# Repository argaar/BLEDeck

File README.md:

# BLEDeck

A custom BLE macro pad controlled by a Windows desktop application. Press a key, run a command. Switch profile, change context. Everything is driven by the app, the device is a pure peripheral.

---

## Overview

BLEDeck is a 4×4 mechanical keypad with per-key RGB lighting, a rotary encoder, and an OLED display, built around an ESP32. It communicates over BLE with a Windows app that maps each key to a shell command or executable. Profiles let you maintain separate key layouts for different workflows.

The device carries no persistent state. Every time the app connects, it pushes the current profile names and key colors to the device. This is by design, the app is the source of truth.

---

## Hardware

| Component | Part |
|-----------|------|
| MCU | ESP32 DevKitC v1 (NodeMCU-32S) |
| Keys | 16 × Gateron switches (CherryMX style) on Kailh hot-swap sockets |
| RGB | 16 × WS2812B-4020 side-emitting SMD LEDs |
| Display | SSD1306 128×64 OLED |
| Encoder | EC11 rotary encoder with push button |
| Extra buttons | CON (confirm) + BACK, mounted beside the encoder |
| Battery | Optional 1S LiPo with 15 kΩ / 4.3 kΩ voltage divider on GPIO 13 |
| PCB | Custom KiCad design, v1.1 (files under `pcb/`) |

---

## Repository Layout

```
BLEDeck/
├── firmware/          PlatformIO project (ESP32 Arduino)
│   └── src/
│       ├── main.cpp            Main loop, BLE callbacks, all handlers
│       ├── configuration.h     Pin map, BLE limits, battery constants
│       ├── protocolparser.h    Binary protocol definition + packet parser
│       ├── ota_manager.h/.cpp  WiFi OTA update manager (ElegantOTA)
│       ├── menu.h              Simple OLED settings menu
│       ├── images.h            XBM splash/lock screen bitmaps
│       └── credentials.h       WiFi + OTA password (gitignored, see below)
├── windows_app/       PyQt5 desktop application
│   ├── main.py                 BLEDeck GUI, BLE lifecycle, notification dispatch
│   ├── key_button.py           KeyButton widget
│   ├── ble_protocol.py         Packet builders, parsers, opcode constants
│   ├── ble_client.py           BleakClient re-export, BLE UUIDs, simulator factory
│   ├── profile_manager.py      Load/save profiles.json
│   ├── app_settings.py         Persistent app-level settings (preferred device MAC, …)
│   ├── action_runner.py        Command/macro dispatch with re-entrancy guard
│   ├── macro_models.py         Immutable step types + JSON serialization
│   ├── macro_recorder.py       pynput-based recorder with window anchor detection
│   ├── macro_player.py         Synchronous macro playback
│   ├── macro_dialog.py         MacroDialog QDialog (record, edit, reorder, test)
│   ├── win32_utils.py          Windows API helpers (window/monitor detection)
│   └── tests/                  Pytest suite
│       ├── test_ble_protocol.py
│       ├── test_profile_manager.py
│       ├── test_action_runner.py
│       └── test_macro_models.py
├── simulator/         BLE device simulator (no hardware needed)
│   ├── __main__.py             Entry point: python -m simulator [--ble]
│   ├── _context.py             Module-level singletons (DeviceState, active client)
│   ├── device_state.py         Simulated device state
│   ├── command_handler.py      PC→Device command handler
│   ├── event_emitter.py        Device→PC event builders
│   ├── ble_server.py           Real BLE via WinRT GattServiceProvider (Mode B)
│   ├── fake_bleak_client.py    In-process loopback (Mode A)
│   ├── cli.py                  Interactive REPL
│   └── tests/                  Pytest suite
├── pcb/               KiCad schematic + layout + Gerbers
├── docs/              Protocol reference and debugging guides
│   ├── ble_protocol_reference.md
│   ├── protocol_debugging.md
│   └── hex_quick_reference.md
└── debug/
    └── protocol_decoder.py     CLI tool to decode raw BLE packets
```

---

## Firmware

Full setup and configuration details: [`firmware/README.md`](firmware/README.md)

### Features

- **BLE GATT server** - custom service with a TX (notify) and RX (write) characteristic
- **Binary protocol** - compact framed packets: `0xAA | OPCODE | LENGTH(2B) | PAYLOAD`; max payload 256 bytes
- **Profile management** - up to 10 profiles; names and current index are pushed by the app on connect
- **Rotary encoder** - cycles through profiles when the app is connected; plays an idle RGB animation when disconnected
- **Per-key RGB** - 16 WS2812B LEDs, colors set individually or all at once by the app
- **OLED display** - shows current profile name, BLE connection status, and battery percentage
- **Battery monitoring** - ADC reading every 30 s, 5-sample rolling average, reported to the app via opcode `0x85`
- **Workstation lock** - when locked by the app, the OLED dims and shows a lock icon; all key events are suppressed
- **OTA updates** - long-press the encoder push button to open the settings menu, select *OTA Update*; the device connects to WiFi (or falls back to an AP) and serves the ElegantOTA web UI
- **`OP_HELLO` / `OP_DEVICE_TELEMETRY` handshake** - on connect the app sends `OP_HELLO` with its protocol/app version, the device replies with telemetry (firmware version, uptime, free heap, BLE error count)
- **OTA HTTP auth rate-limit infrastructure** - 5 failed logins within 60 s trigger a 5-minute lockout (trigger awaits an ElegantOTA upstream hook)

### Firmware Setup

1. Install [PlatformIO](https://platformio.org/).
2. Copy `firmware/src/credentials.h.example` → `firmware/src/credentials.h` and fill in:
   ```cpp
   #define OTA_WIFI_SSID     "your_ssid"
   #define OTA_WIFI_PASSWORD "your_wifi_password"
   #define OTA_HTTP_PASSWORD "your_ota_http_password"
   ```
3. Build and flash:
   ```bash
   cd firmware
   pio run --target upload
   ```

### Build a personalized firmware via GitHub Actions (no toolchain)

Don't want to install PlatformIO? You can have GitHub build a firmware binary
with **your own** WiFi + OTA credentials baked in and email it to you. The
`Build Personalized Firmware` workflow handles it.

1. **Fork** this repository to your own GitHub account (Actions and secrets run
   under your fork, not the upstream repo).
2. In your fork, add two repository secrets under
   **Settings → Secrets and variables → Actions → New repository secret**:
   - `MAIL_USERNAME` — the Gmail address that sends the build
   - `MAIL_PASSWORD` — a Gmail [App Password](https://support.google.com/accounts/answer/185833)
     for that account (requires 2-Step Verification; your normal password will
     not work)
3. Open the **Actions** tab → **Build Personalized Firmware** →
   **Run workflow**, and fill in:
   - `wifi_ssid`, `wifi_password` — the network the device joins for OTA
   - `ota_http_password` — the password for the OTA upload page
   - `recipient_email` — where to send the finished `firmware.bin`
4. Wait for the run to finish (a few minutes). The compiled `firmware.bin`
   arrives by email; flash it to the ESP32 with ElegantOTA or `esptool`.

> **Spam note:** the email is sent from a personal Gmail account with an
> attachment, so it can land in **Spam/Junk**. If it doesn't show up in your
> inbox within a few minutes, check there and mark it *Not spam*.

> **Privacy note:** the credentials you enter are masked in the build logs and
> the generated `credentials.h` is deleted at the end of the run, but the
> finished binary still contains them and travels through Gmail. Use this for
> personal networks, not shared/sensitive ones.

---

## Windows App

Full setup and usage details: [`windows_app/README.md`](windows_app/README.md)

### Features

- Scan and connect to BLEDeck over BLE (auto-reconnect optional)
- **Per-key configuration** - label, RGBW color (with color picker + brightness slider), action
- **Two action types per key** - shell command (via `subprocess`) or recorded macro
- **Macro recorder** - capture mouse clicks and keystrokes; replay them on key press
  - Per-click window/monitor-relative coordinates: clicks are anchored to the window or monitor they were recorded on, so playback works even if windows have moved
  - Multi-monitor support: monitors indexed by left edge (0 = leftmost)
  - Edit individual steps, drag-to-reorder, delete steps, test-run from the dialog
- **Profile management** - create, rename, save, and delete profiles; stored in `profiles.json`
- **Live RGB sync** - changing a key color sends the update to the device immediately
- **Battery indicator** - displays the battery percentage reported by the device
- **System tray** - minimises to tray, double-click or single-click to restore
- On connect: pushes all profile names, then the current profile index + RGB colors
- **Rotating debug log** at `%APPDATA%\BLEDeck\logs\bledeck.log` (5 × 20 MB rotation, 100 MB cap; KEEP_ALIVE traffic filtered out)
- **Preferred device MAC pinning** + **exponential reconnect backoff** (10 s → doubles per failed attempt → 5 min cap; resets on success)
- **High-risk command-token warning** on profile load — flags commands containing tokens such as `powershell`, `cmd /c`, `iex`, `curl … | iex`, `bitsadmin`, `mshta` before they can run
- **Macro recorder auto-stop** after 60 s of idle keyboard / mouse activity

### App Setup

```bash
cd windows_app
pip install -r requirements.txt
python main.py
```

> Python 3.12 or later required. Tested on Windows 11.

### Development Without Hardware

A device simulator is included — no physical BLEDeck required.

Loopback mode (default): no Bluetooth, instant connect. Pick the row for your shell:

| Shell       | Command |
|-------------|---------|
| cmd.exe     | `set BLEDECK_SIM=1 && python windows_app\main.py` |
| PowerShell  | `$env:BLEDECK_SIM=1; python windows_app\main.py` |
| Git Bash    | `BLEDECK_SIM=1 python windows_app/main.py` |

Real BLE mode (two machines): simulator on Machine A, app on Machine B:

```bash
python -m simulator --ble
```

Full details: [`simulator/README.md`](simulator/README.md)

---

## BLE Protocol

Full reference: [`docs/ble_protocol_reference.md`](docs/ble_protocol_reference.md)

| Direction | Opcodes |
|-----------|---------|
| PC → Device | `0x01` KEEP_ALIVE, `0x02` CHANGE_PROFILE, `0x03` SYNC_PROFILES, `0x04` SET_RGB_KEY, `0x05` SET_ALL_RGB_KEYS, `0x06` LOCK_DEVICE, `0x07` HELLO |
| Device → PC | `0x81` KEEP_ALIVE_REPLY, `0x82` PROFILE_CHANGED, `0x83` BUTTON_PRESSED, `0x84` KEY_PRESSED, `0x85` BATTERY_STATUS, `0x86` DEVICE_TELEMETRY |

To decode a raw packet from the log:
```bash
cd debug
python protocol_decoder.py "aa 85 00 01 48"
# or interactive:
python protocol_decoder.py
```

For advanced debugging see [`docs/protocol_debugging.md`](docs/protocol_debugging.md)
If you're interested in understanding the protocol, take a look at [`docs/hex_quick_reference.md`](docs/hex_quick_reference.md)

---

## Intended Use

BLEDeck is designed for Windows power users who want a physical shortcut pad without writing firmware macros. Key assignments live entirely in the app, change them without reflashing.

Typical profiles:
- **Dev** - open IDE, terminal, browser, run build script
- **Media** - control Spotify, OBS, volume
- **Gaming** - push-to-talk, clips, Discord mute
- **Comms** - join meeting, mute mic, share screen

The rotary encoder switches between profiles. The three encoder-side buttons (CON, BACK, PUSH) send named button events to the app, which can be mapped to any action.

---

## Limitations

- **Windows only** - the desktop app uses PyQt5, bleak, and ctypes Win32 APIs; no macOS or Linux app exists yet
- **App required** - the device does not persist colors or profile names; it resets to defaults when the app disconnects. This is intentional
- **10 profiles max, 16 keys per profile**
- **BLE range** - approximately 10 m in open space; walls reduce this
- **Battery gauge accuracy** - ±5%, based on a two-resistor voltage divider and a 5-sample average; calibrated for 1S LiPo (3.2 V – 4.2 V)
- **Macro recorder captures press events only** - release timing and mouse movement paths are not recorded

---

## PCB

Custom two-layer board designed in KiCad. Gerbers for JLCPCB are included under `pcb/`. Parts list and supplier links are in [`pcb/README.md`](pcb/README.md).

Current version: **v1.1**

---

## STLs

3D Models ready to be printed in PLA are available under `enclosure/stls` folder.

Ideally you need to assemble parts in the order:

- [PushButton.stl](enclosure/stls/PushButton.stl) (x2)
- [KeyboardLayer.stl](enclosure/stls/KeyboardLayer.stl)
- [BatteryTop.stl](enclosure/stls/BatteryTop.stl)
- [BatteryLayer.stl](enclosure/stls/BatteryLayer.stl)
- [Bottom.stl](enclosure/stls/Bottom.stl)

---

## License

Firmware and application source code are licensed under the [MIT License](LICENSE).

Hardware design files (PCB, schematics) and third-party component symbols/footprints retain their original licenses as listed in [`pcb/README.md`](pcb/README.md). The custom `oledknob.step` footprint is non-commercial use only.

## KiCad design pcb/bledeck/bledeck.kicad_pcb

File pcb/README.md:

# Parts list

### LED RGB WS2812b SMD 4020
https://jlcpcb.com/partdetail/Worldsemi-WS2812B4020/C965557

### Through Hole Resistor 2.2*6.5 250mW (15k + 4.3k)
Battery voltage divider on GPIO 13 (R1=15k top to BAT+, R2=4.3k bottom to GND).
https://jlcpcb.com/partdetail/59662-MFR0W4F1502A50/C58617
https://jlcpcb.com/partdetail/NTEElectronics-QW243/C6262373

### ESP32 DevKitC v1
https://lastminuteengineers.com/esp32-pinout-reference/
https://www.adrirobot.it/modulo-esp32-devkit-v1-con-wifi-e-bluetooth-ble/

### OLED (SSD1306) + Knob (EC11 rotary encoder)
https://it.aliexpress.com/item/1005009186762942.html

### Gateron Switches (CherryMX Style)
https://keychron.it/products/gateron-g-pro-3-0-switch?variant=51681846395247
https://it.aliexpress.com/item/1005006376024657.html

### Switch Transparent Cover
https://it.aliexpress.com/item/1005006821410180.html

### Kahil Hot swappable sockets
https://splitkb.com/products/kailh-hotswap-sockets
https://www.amazon.it/dp/B0DJKTNDHF
https://it.aliexpress.com/item/1005004654079817.html

### Adesive TPU Pads
https://it.aliexpress.com/item/1005006390636772.html

# Resources licenses

### Symbols

- ESP32-DEVKIT-V1.kicad_sym - https://www.snapeda.com/parts/ESP32-DEVKIT-V1/Do+it/view-part/ - CC-BY-SA
- PG151101S11.kicad_sym - https://www.snapeda.com/parts/PG151101S11/Kailh/view-part/ - CC-BY-SA
- WS2812B-4020.kicad_sym - https://www.snapeda.com/parts/WS2812B-4020/Worldsemi/view-part/ - CC-BY-SA

### Footprints

- MODULE_ESP32_DEVKIT_V1.kicad_mod - https://www.snapeda.com/parts/ESP32-DEVKIT-V1/Do+it/view-part/ - CC-BY-SA
- Kailh_socket_MX.kicad_mod - https://github.com/daprice/keyswitches.pretty - CC-BY-SA 4
- oled_rotary.kicad_mod - Custom Made under MIT License
- PinHeader_1x02_P2.54mm_Vertical.kicad_mod - https://gitlab.com/kicad/libraries/kicad-footprints/ - CC-BY-SA 4
- WS2812B-4020.kicad_mod - https://www.snapeda.com/parts/WS2812B-4020/Worldsemi/view-part/ - CC-BY-SA

### 3D Models

- CherryMX Switch.step - https://github.com/foostan/kbd - MIT
- ESP32-DEVKIT-V1.step - https://www.snapeda.com/parts/ESP32-DEVKIT-V1/Do+it/view-part/ - CC-BY-SA
- kailh_hotswap_socket.step - https://www.snapeda.com/parts/PG151101S11/Kailh/view-part/ - CC-BY-SA
- oledknob.step - https://grabcad.com/library/1-3-oled-ec11-1 - No commercial use
- WS2812B-4020--3DModel-STEP-269445.STEP - https://www.snapeda.com/parts/WS2812B-4020/Worldsemi/view-part/ - CC-BY-SA

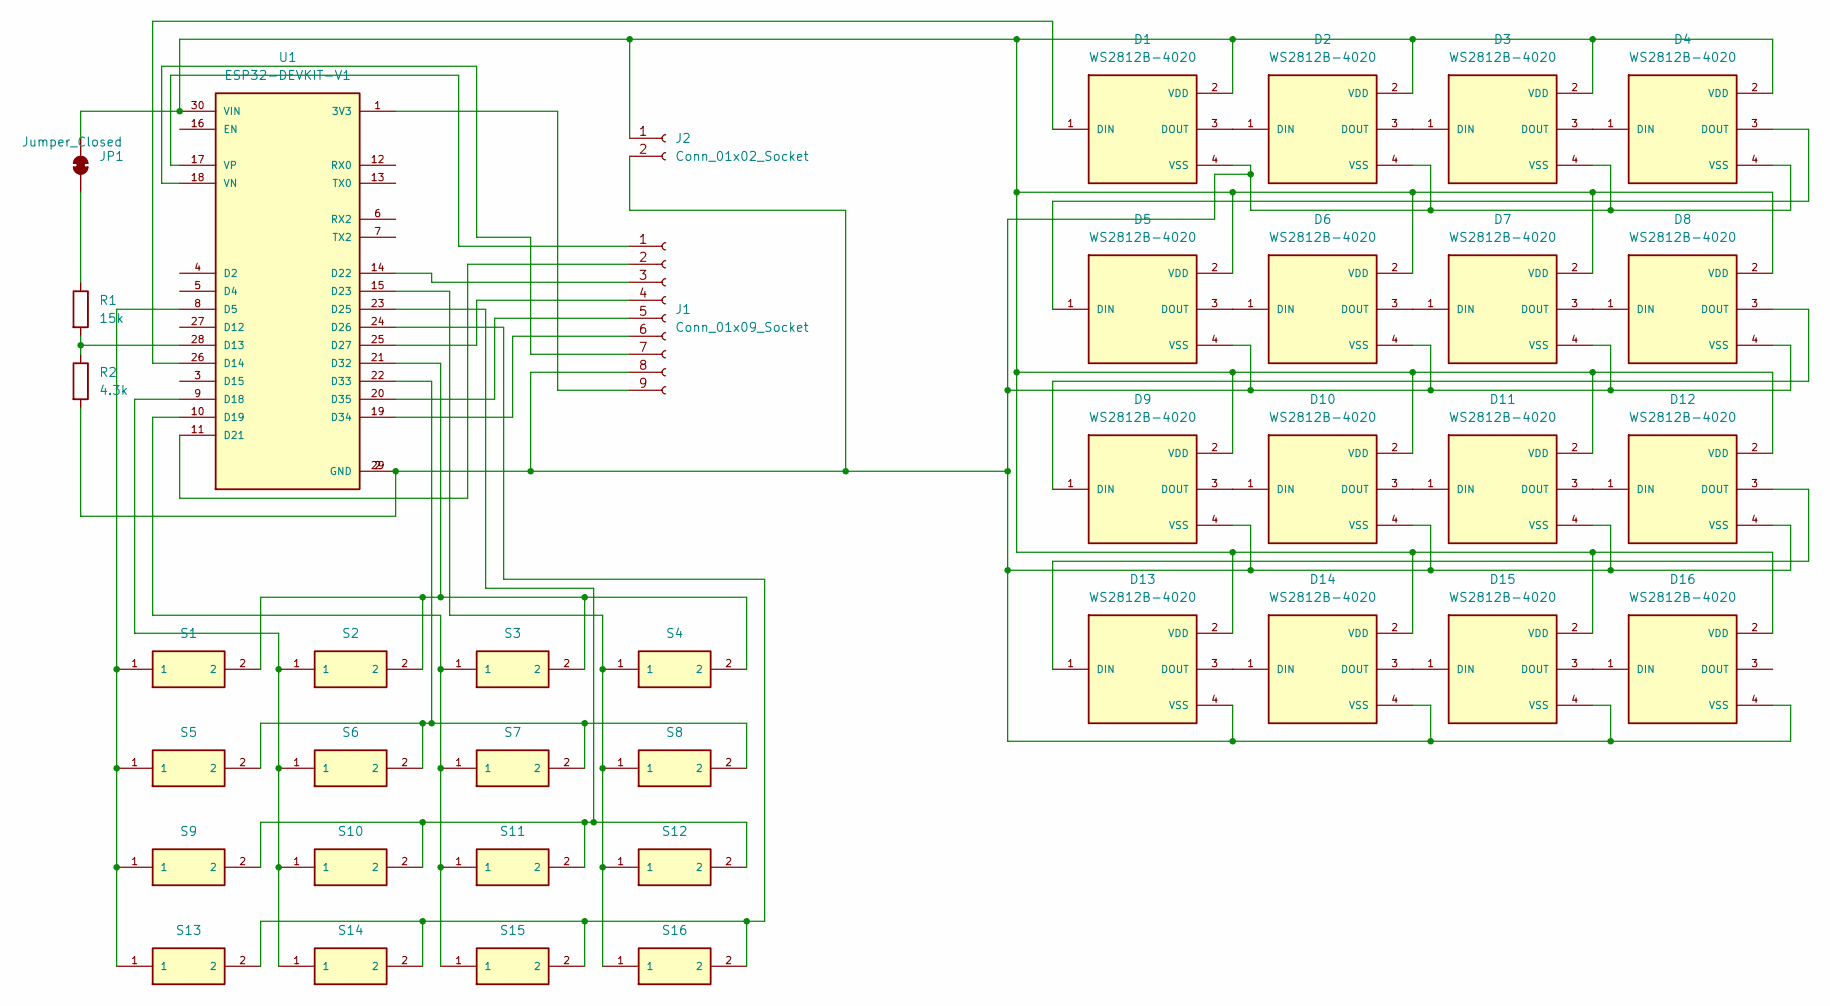
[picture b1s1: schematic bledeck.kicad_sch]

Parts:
D1, D2, D3, D4, D5, D6, D7, D8, D9, D10, D11, D12, D13, D14, D15, D16: WS2812B-4020; PARTREV V1.2
J1: Conn_01x09_Socket; oled_rotary
J2: Conn_01x02_Socket; PinHeader_1x02_P2.54mm_Vertical
JP1: Jumper_Closed; PinHeader_1x02_P2.54mm_Vertical
R1: 15k; R_Axial_DIN0207_L6.3mm_D2.5mm_P7.62mm_Horizontal
R2: 4.3k; R_Axial_DIN0207_L6.3mm_D2.5mm_P7.62mm_Horizontal
S1, S2, S3, S4, S5, S6, S7, S8, S9, S10, S11, S12, S13, S14, S15, S16: PG151101S11; SW_PG151101S11; PARTREV A
U1: ESP32-DEVKIT-V1; MODULE_ESP32_DEVKIT_V1; PARTREV N/A

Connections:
unnamed: D1.1 (DIN), U1.26 (D14)
unnamed: D1.3 (DOUT), D2.1 (DIN)
unnamed: D1.2 (VDD), D2.2 (VDD), D3.2 (VDD), D4.2 (VDD), D5.2 (VDD), D6.2 (VDD), D7.2 (VDD), D8.2 (VDD), D9.2 (VDD), D10.2 (VDD), D11.2 (VDD), D12.2 (VDD), D13.2 (VDD), D14.2 (VDD), D15.2 (VDD), D16.2 (VDD), J2.1, JP1.2 (B), U1.30 (VIN)
unnamed: D1.4 (VSS), D2.4 (VSS), D3.4 (VSS), D4.4 (VSS), D5.4 (VSS), D6.4 (VSS), D7.4 (VSS), D8.4 (VSS), D9.4 (VSS), D10.4 (VSS), D11.4 (VSS), D12.4 (VSS), D13.4 (VSS), D14.4 (VSS), D15.4 (VSS), D16.4 (VSS), J1.8, J2.2, R2.2, U1.2 (GND), U1.29 (GND)
unnamed: D2.3 (DOUT), D3.1 (DIN)
unnamed: D3.3 (DOUT), D4.1 (DIN)
unnamed: D4.3 (DOUT), D5.1 (DIN)
unnamed: D5.3 (DOUT), D6.1 (DIN)
unnamed: D6.3 (DOUT), D7.1 (DIN)
unnamed: D7.3 (DOUT), D8.1 (DIN)
unnamed: D8.3 (DOUT), D9.1 (DIN)
unnamed: D9.3 (DOUT), D10.1 (DIN)
unnamed: D10.3 (DOUT), D11.1 (DIN)
unnamed: D11.3 (DOUT), D12.1 (DIN)
unnamed: D12.3 (DOUT), D13.1 (DIN)
unnamed: D13.3 (DOUT), D14.1 (DIN)
unnamed: D14.3 (DOUT), D15.1 (DIN)
unnamed: D15.3 (DOUT), D16.1 (DIN)
unnamed: J1.1, U1.17 (VP)
unnamed: J1.2, U1.11 (D21)
unnamed: J1.3, U1.14 (D22)
unnamed: J1.4, U1.25 (D27)
unnamed: J1.5, U1.20 (D35)
unnamed: J1.6, U1.19 (D34)
unnamed: J1.7, U1.18 (VN)
unnamed: J1.9, U1.1 (3V3)
unnamed: JP1.1 (A), R1.1
unnamed: S1.1, S5.1, S9.1, S13.1, U1.8 (D5)
unnamed: R1.2, R2.1, U1.28 (D13)
unnamed: S2.1, S6.1, S10.1, S14.1, U1.9 (D18)
unnamed: S3.1, S7.1, S11.1, S15.1, U1.10 (D19)
unnamed: S4.1, S8.1, S12.1, S16.1, U1.15 (D23)
unnamed: S9.2, S10.2, S11.2, S12.2, U1.23 (D25)
unnamed: S13.2, S14.2, S15.2, S16.2, U1.24 (D26)
unnamed: S1.2, S2.2, S3.2, S4.2, U1.21 (D32)
unnamed: S5.2, S6.2, S7.2, S8.2, U1.22 (D33)

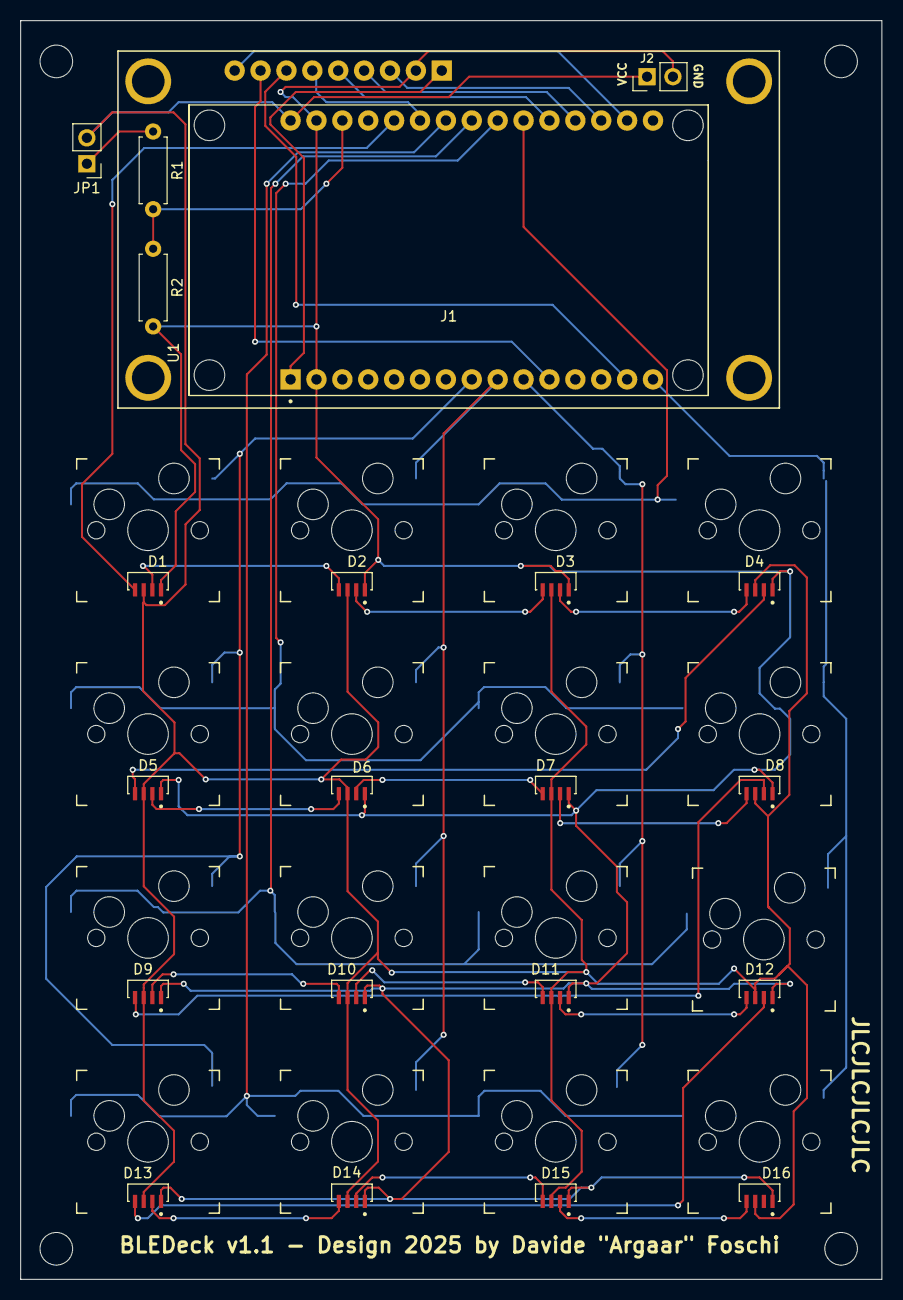
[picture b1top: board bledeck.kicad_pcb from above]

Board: 2 copper layers, 84.5 x 123.5 mm, 38 parts (0 on the bottom side), 36 nets.

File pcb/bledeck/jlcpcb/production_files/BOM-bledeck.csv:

Comment,Designator,Footprint,LCSC,Quantity
PG151101S11,S16,Kailh_socket_MX,,1
PG151101S11,S14,Kailh_socket_MX,,1
PG151101S11,S10,Kailh_socket_MX,,1
PG151101S11,S4,Kailh_socket_MX,,1
Conn_01x09_Socket,J1,oled_rotary,,1
WS2812B-4020,D13,WS2812B-4020,,1
PG151101S11,S15,Kailh_socket_MX,,1
PG151101S11,S12,Kailh_socket_MX,,1
WS2812B-4020,D7,WS2812B-4020,,1
PG151101S11,S7,Kailh_socket_MX,,1
WS2812B-4020,D10,WS2812B-4020,,1
PG151101S11,S11,Kailh_socket_MX,,1
WS2812B-4020,D15,WS2812B-4020,,1
PG151101S11,S8,Kailh_socket_MX,,1
Conn_01x02_Socket,J2,PinHeader_1x02_P2.54mm_Vertical,,1
PG151101S11,S6,Kailh_socket_MX,,1
PG151101S11,S9,Kailh_socket_MX,,1
WS2812B-4020,D11,WS2812B-4020,,1
WS2812B-4020,D2,WS2812B-4020,,1
PG151101S11,S2,Kailh_socket_MX,,1
ESP32-DEVKIT-V1,U1,MODULE_ESP32_DEVKIT_V1,,1
WS2812B-4020,D14,WS2812B-4020,,1
WS2812B-4020,D3,WS2812B-4020,,1
PG151101S11,S13,Kailh_socket_MX,,1
PG151101S11,S5,Kailh_socket_MX,,1
WS2812B-4020,D6,WS2812B-4020,,1
WS2812B-4020,D5,WS2812B-4020,,1
PG151101S11,S1,Kailh_socket_MX,,1
WS2812B-4020,D4,WS2812B-4020,,1
WS2812B-4020,D1,WS2812B-4020,,1
WS2812B-4020,D16,WS2812B-4020,,1
WS2812B-4020,D12,WS2812B-4020,,1
WS2812B-4020,D9,WS2812B-4020,,1
PG151101S11,S3,Kailh_socket_MX,,1
WS2812B-4020,D8,WS2812B-4020,,1
15k,R1,R_Axial_DIN0207_L6.3mm_D2.5mm_P7.62mm_Horizontal,,1
4.3k,R2,R_Axial_DIN0207_L6.3mm_D2.5mm_P7.62mm_Horizontal,,1

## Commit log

2025-10-28 change profiles format, add color, add colorpicker, other fixes
2025-10-28 change display, fix key label
2025-11-10 add pcb
2025-11-11 generate gerber, fix pin number
2025-11-11 pcb add libraries and readme with licenses
2025-11-11 add assets dir
2025-11-13 add locked and rgb support
2025-11-13 add missing file from previous commit
2025-11-13 add support for rgb
2025-11-17 increase display messages size
2025-11-20 switch ble protocol to binary format, add docs to document protocol, add debug scripts to test protocol data, fix some issues in both app and firmware
2025-11-20 remove prefs, fix rgb key in code and docs, remove profile+rgb payload when switching, remove unused code, small improvements in firmware
2025-11-20 fix locked state, add rgb animation when idle
2025-11-20 remove unused code, code quality
2025-11-24 fix bug in single rgb sync, add pynput as dependecy in order to support macro inputs, update dependecies, fix protocol_decoder
2025-11-27 [firmware] add battery info [pcb] evenly spaced keys, fix oled pins position, reroute all tracks/vias, add gerber zip for jlcpcb
2025-12-16 [firmware] add battery to display, fix oledupdate [pcb] fix keys connections, fix led traces, fix oled footprint [misc] add parts list to Readme
2025-12-18 [firmware] fix battery mgmt
2025-12-18 [firmware] add ifdef for adc attenuation
2026-01-13 [pcb] version 1.1 [firmware] enabled 16 rgb, change keys layout
2026-03-12 upload stl files for 3d print encloure
2026-04-29 add readme for each subproject, add general readme, add battery report via bt to app, add ota support with elegant ota, change partition layout to free up some space add wifi support to flash new fir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
2026-04-29 fix stls
2026-04-29 fix in some Readme files
2026-04-29 fix last readme files
2026-05-03 fix locked workstation detected
2026-05-05 fix keyboard stl
2026-05-05 Remove file reference from README
2026-05-07 create per folder gitignore files, decrease hole size for keyboardlayer stl
2026-05-08 add link to debugging and hex reference, fix gitignore
2026-05-15 [windows_app] fix 2 bugs, clean dead code, extract KeyButton, add type hints, consolidate color parsing, add 39 tests [common] update readme
2026-05-23 [windows_app] small fixes, new tests added
2026-05-23 [windows_app] fix reconnecting issue, update dependencies to latest version
2026-05-23 [windows_app] add macro support, update Readme
2026-05-23 [windows_app] add installer to package python code as window executable
2026-05-30 [common] add open-source meta, simulator, firmware tests, app hardening
    Project meta:
    - add LICENSE, CONTRIBUTING.md, CHANGELOG.md, PR template, pyproject.toml
    - add run-tests.sh/.bat, docs/troubleshooting.md
    [simulator] new component: in-process FakeBleakClient loopback (Mode A) +
    WinRT GATT server (Mode B), CLI REPL, command_handler/event_emitter
    sharing ble_protocol.py, full pytest suite
2026-05-30 [misc] add CI test workflow [docs] add 3D renders to README
    [misc] .github/workflows/tests.yml — runs firmware native (Unity) on
    ubuntu and the Python suites (windows_app + simulator) on windows.
    Triggers: manual dispatch (with all/firmware/python selector), push to
    main, and pull_request.
    [docs] README: embed assets/3d_renders images (front, side, keys, hot-swap
    connectors) and add a Tests workflow status badge.
2026-05-30 [misc] add Windows app build workflow on release
    .github/workflows/build-windows.yml — runs windows_app/build.bat
    (PyInstaller via bledeck.spec) on windows-latest. On a published GitHub
    release, zips dist/BLEDeck/ and attaches it as a release asset; on manual
    dispatch, uploads the zip as a run artifact only.
2026-05-30 [misc] bump CI actions to Node 24, fix double-zip in build artifact
    - Silence Node 20 deprecation: checkout@v5, setup-python@v6,
    upload-artifact@v5, and set FORCE_JAVASCRIPT_ACTIONS_TO_NODE24 to push
    the remaining Node 20 action (cache@v4) onto Node 24.
    - build-windows: upload-artifact now points at the dist/BLEDeck/ folder
    (it zips its own input) instead of a pre-made zip, fixing the
    zip-inside-a-zip download. Release asset still zipped explicitly as
2026-05-30 [misc] silence CI Node 20 warning and windows-latest redirect notice
    - Drop the optional PlatformIO cache step (actions/cache@v4 has no Node 24
    major and still warns even when forced); native build is fast without it.
    Removes the now-unneeded FORCE_JAVASCRIPT_ACTIONS_TO_NODE24 env.
    - Pin Windows jobs to windows-2025 (windows-latest is being redirected to
    windows-2025-vs2026 by June 2026).
2026-05-30 [misc] add personalized firmware build-and-email workflow
    .github/workflows/build.yml — manual dispatch takes WiFi SSID/password,
    OTA HTTP password, and a recipient email; masks the secrets, generates a
    gitignored credentials.h from credentials.h.example, builds the
    nodemcu-32 firmware via PlatformIO, emails firmware.bin via Gmail SMTP
    (MAIL_USERNAME/MAIL_PASSWORD secrets), and deletes credentials.h on exit.
2026-05-30 [misc] fix notice on windows actions
2026-05-30 [misc] fix firmware build workflow, rename build workflows
    - build-personalized-firmware: replace nonexistent
    native-instruments/setup-platformio-core-action (404) with
    setup-python@v6 + pip install platformio, matching tests.yml.
    - build-windows-app: set FORCE_JAVASCRIPT_ACTIONS_TO_NODE24=true env.
    - rename build.yml -> build-personalized-firmware.yml and
    build-windows.yml -> build-windows-app.yml for clarity.
2026-05-30 [misc] fix credential leak in personalized firmware workflow
    workflow_dispatch inputs are not auto-masked, and the runner prints each
    step's env: block in plaintext at step start — so defining the inputs as
    job-level env exposed WiFi/OTA credentials in the logs (public on a public
    repo). Read the inputs from $GITHUB_EVENT_PATH at runtime, ::add-mask::
    them, and re-export via $GITHUB_ENV instead. No env: key carries the
    secrets anymore.
2026-05-30 [windows_app] fix 3 Dependabot alerts (markdown, pytest) [misc] harden firmware mail workflow
    [windows_app]
    - markdown 3.7 -> 3.10.2: PYSEC-2026-89, unhandled AssertionError DoS on
    malformed Markdown (only renders the bundled manual.md here, but clears
    the alert in pyproject.toml + requirements.txt).
    - pytest <9 -> >=9.0.3: CVE-2025-71176, predictable /tmp/pytest-of-* dir
    on UNIX. Lifted the stale pytest-asyncio<1 cap to >=1.4 (supports pytest
2026-05-30 [misc] fix notice in tests action
2026-05-30 [docs] document personalized firmware build via GitHub Actions
    README: add a Firmware section walkthrough for the Build Personalized
    Firmware workflow — fork, set MAIL_USERNAME/MAIL_PASSWORD (Gmail App
    Password) secrets, dispatch with WiFi/OTA/recipient inputs, receive the
    binary by email. Includes a spam-folder note and a privacy note.
